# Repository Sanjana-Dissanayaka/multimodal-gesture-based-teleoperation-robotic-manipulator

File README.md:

# Multimodal Gesture-Based Teleoperation Framework for Low-Cost Robotic Manipulators

A low-cost gesture-based robotic teleoperation framework designed to provide an intuitive human–robot interaction interface using a wearable sensor glove.

The current system combines an **MPU6050 inertial measurement unit (IMU)** and **flex sensors** with calibration, filtering, gesture recognition, VPython hand visualization, and inverse-kinematics-based robotic manipulator control.

The framework is being extended toward a **hybrid multimodal teleoperation system** by integrating computer-vision-based hand tracking and physical robotic manipulator validation.

---

## Project Overview

Conventional robotic manipulator teleoperation interfaces such as joysticks and teach pendants can be less intuitive when operators need to perform natural hand-based manipulation.

Gesture-based interfaces provide a more natural method of communicating human intent to a robotic system. However, systems that depend on only one sensing method may experience problems such as:

* Sensor drift
* Measurement noise
* Camera occlusion
* Lighting variation
* Limited gesture information
* High implementation cost
* Reduced teleoperation accuracy

This project investigates a low-cost teleoperation framework that initially uses a wearable **IMU + flex-sensor glove** and is designed to later combine wearable sensing with computer vision.

---

## Overall Objective

Develop and validate a low-cost hybrid teleoperation system that integrates an **IMU + flex-sensor glove** with computer-vision-based hand tracking to achieve robust, accurate, and intelligent robotic manipulator control.

---

## System Architecture

The current teleoperation pipeline can be represented as:

```text
Human Hand
    │
    ▼
IMU + Flex Sensor Glove
    │
    ▼
Microcontroller / Data Acquisition
    │
    ▼
Calibration + Filtering
    │
    ▼
Gesture Recognition + Orientation Estimation
    │
    ├──────────────► VPython Virtual Hand
    │
    ▼
Gesture / Orientation Command Mapping
    │
    ▼
Inverse Kinematics
    │
    ▼
Robotic Manipulator Simulation
    │
    ▼
Sorting / Pick-and-Place Tasks
```

The planned multimodal extension is:

```text
Wearable Sensor Glove ──────┐
                            │
                            ▼
                    Hybrid Sensor Fusion
                            ▲
                            │
RGB Camera + MediaPipe ─────┘
                            │
                            ▼
                Robotic Manipulator Control
```

---

## Current Implementation

### 1. Wearable Sensing Layer

The wearable glove provides information about hand orientation and finger movement.

**MPU6050 IMU**

Used to estimate:

* Roll
* Pitch
* Yaw

**Flex Sensors**

Used to detect:

* Finger bending
* Open-hand gestures
* Closed-hand gestures
* Finger-count gestures
* Object-selection commands

---

## 2. Sensor Acquisition and Stabilization

Raw sensor data can contain noise, offsets, and small fluctuations.

The system therefore applies:

* Startup neutral calibration
* Flex-sensor calibration
* IMU calibration
* Deadband processing
* First-order smoothing
* Gesture stabilization
* Threshold-based gesture classification

These techniques improve the stability of commands before they are transmitted to the robotic manipulator.

---

## 3. Flex-Sensor Gesture Validation

The current gesture-validation criteria include:

| Condition           | Approximate Threshold |
| ------------------- | --------------------: |
| Straight finger     |                 ≤ 25° |
| Bent finger         |                 ≥ 60° |
| Stable gesture hold |                 0.5 s |

A gesture must remain sufficiently stable before it is accepted as a control command.

This helps prevent accidental commands caused by temporary sensor fluctuations.

---

## 4. Gesture Mapping

Finger gestures are mapped to object-selection and manipulation commands.

| Gesture   | Command              |
| --------- | -------------------- |
| 1 finger  | Select RED object    |
| 2 fingers | Select BLUE object   |
| 3 fingers | Select GREEN object  |
| 4 fingers | Select YELLOW object |
| Fist      | PICK                 |
| Open palm | PLACE / RELEASE      |

This allows the operator to select and manipulate objects using natural hand gestures.

---

## 5. IMU Orientation Mapping

The MPU6050 provides orientation information for controlling the manipulator end effector.

| Human-Hand Motion | Robot Command      |
| ----------------- | ------------------ |
| Roll              | End-effector roll  |
| Pitch             | End-effector pitch |
| Yaw               | End-effector yaw   |

Control limits are applied to prevent unrealistic or unstable manipulator commands.

### Current Safety Limits

| Motion       | Limit |
| ------------ | ----: |
| Roll         |  ±35° |
| Pitch        |  ±35° |
| Yaw          |  ±60° |
| Command rate | 25 Hz |

---

## 6. Virtual Hand Validation

Before controlling the robotic manipulator, sensor information is visualized using **VPython**.

The virtual-hand environment is used to validate:

* Finger bending
* Hand orientation
* Open-palm detection
* Fist detection
* Finger-count gestures
* Sensor calibration
* Gesture stability

This provides an intermediate validation stage between the physical glove and robotic manipulator.

---

## 7. Robotic Manipulator Simulation

Robotic manipulation is investigated using simulation environments such as:

* PyBullet
* CoppeliaSim

The simulation stage includes:

* Manipulator kinematics
* Forward kinematics
* Inverse kinematics
* End-effector orientation control
* Gesture-to-command mapping
* Object selection
* Pick-and-place operations
* Object sorting
* Contact-based manipulation experiments

---

## Inverse Kinematics

The desired end-effector pose generated from the gesture interface is converted into manipulator joint commands using inverse kinematics.

The general control process is:

```text
Human Gesture
      ↓
Target End-Effector Pose
      ↓
Inverse Kinematics
      ↓
Required Joint Angles
      ↓
Manipulator Motion
```

Inverse kinematics allows intuitive hand commands to be translated into feasible robotic manipulator movements.

---

## Hardware

The project hardware platform includes or investigates:

* MPU6050 IMU
* Flex sensors
* Wearable glove
* Microcontroller
* Custom PCB
* CH340G USB communication interface
* Flex-sensor interface circuitry
* Sensor wiring and connectors
* Robotic manipulator for final physical testing
* RGB camera for the planned vision stage

---

## Software and Development Tools

### Current Tools

* Python
* VPython
* PyBullet
* CoppeliaSim
* Arduino IDE
* KiCad
* Git
* GitHub

### Planned Vision Tools

* OpenCV
* MediaPipe

### Analysis and Evaluation

* Python
* MATLAB

---

## Major Development Phases

### Phase 1 – Wearable Hardware Development

* System architecture development
* PCB design
* Embedded firmware
* Hardware integration

### Phase 2 – Sensor Acquisition and Calibration

* MPU6050 calibration
* Flex-sensor calibration
* Noise filtering
* Gesture stabilization
* Wearable glove fabrication

### Phase 3 – Virtual Hand and Manipulator Validation

* VPython visualization
* Gesture mapping
* Teleoperation data acquisition
* Manipulator simulation
* Inverse-kinematics control

### Phase 4 – Vision-Based Teleoperation

Planned development includes:

* MediaPipe hand tracking
* Vision gesture recognition
* Vision-only manipulator control
* Performance comparison with the sensor glove

### Phase 5 – Hybrid Sensor Fusion

The future multimodal framework will combine:

```text
IMU
 +
Flex Sensors
 +
Computer Vision
        ↓
Hybrid Gesture Estimation
        ↓
Robotic Manipulator Control
```

The aim is to improve robustness against problems such as sensor drift and camera occlusion.

### Phase 6 – Physical Robot Integration

The final stage is intended to include:

* Physical robotic manipulator integration
* Wireless master–slave communication
* Servo-control optimization
* Real-time physical teleoperation
* Pick-and-place experiments
* Robustness testing
* Latency measurement
* Trajectory analysis
* Statistical evaluation

---

## Key Features

* Low-cost wearable gesture interface
* MPU6050-based hand orientation estimation
* Flex-sensor finger-motion measurement
* Sensor calibration
* Deadband processing
* Signal smoothing
* Stable gesture detection
* VPython virtual-hand visualization
* Gesture-labelled object selection
* Inverse-kinematics-based manipulator control
* PyBullet/CoppeliaSim simulation
* Pick-and-place control
* Object sorting
* Extendable multimodal architecture
* Planned MediaPipe computer-vision integration
* Designed for physical robotic-manipulator validation

---

## Research Contribution

The current framework provides a practical foundation for an intuitive and cost-effective human–robot teleoperation interface.

The main research direction is the development of a multimodal system that combines the advantages of wearable sensors and computer vision.

Potential benefits include:

* Improved teleoperation robustness
* Reduced dependence on conventional joysticks
* Natural human–robot interaction
* Improved resistance to camera occlusion
* Compensation for wearable-sensor drift
* Low implementation cost
* Flexible gesture-to-robot mapping

---

---
 ## Project Status

### Completed / Demonstrated

* Wearable gesture-glove prototype
* MPU6050 sensor acquisition
* Flex-sensor acquisition
* Sensor calibration
* Signal smoothing and deadband
* Gesture recognition
* VPython virtual-hand visualization
* Gesture-to-command mapping
* Manipulator simulation
* Inverse-kinematics-based control
* Gesture-controlled sorting and pick-and-place demonstrations

### Next Development Stage

* RGB-camera integration
* MediaPipe hand tracking
* Vision-only teleoperation
* Comparison between glove and vision systems
* Hybrid sensor fusion
* Physical robotic manipulator integration
* Experimental performance evaluation

---

## Future Improvements

* MediaPipe hand-landmark tracking
* Adaptive multimodal sensor fusion
* Vision and wearable-sensor synchronization
* Automatic sensor-drift compensation
* Kalman or complementary filtering
* Improved gesture-classification algorithms
* Wireless glove communication
* Physical 6-DoF manipulator integration
* End-effector camera feedback
* Collision avoidance
* Workspace constraints
* Trajectory smoothing
* Latency optimization
* Gesture confusion-matrix analysis
* Quantitative trajectory-error analysis
* User-based teleoperation experiments

---

## Contributors

### Lowe W.N.D.

**Registration No.: 2022/E/172**

Primary areas include:

* Embedded electronics
* PCB development
* IMU and flex-sensor calibration
* Python development
* Sensor fusion
* Teleoperation implementation
* Experimental evaluation

### Dissanayaka W.A.M.S.K.

**Registration No.: 2022/E/174**

Primary areas include:

* VPython visualization
* PyBullet simulation
* Computer vision
* MediaPipe implementation
* Mechanical fabrication
* Sensor-fusion development
* Experimental evaluation
* Documentation

---

## Supervisors

**Supervisor:** Mr. M. Barathraj
**Co-Supervisor:** Mr. P. Ravivarman

Department of Electrical & Electronic Engineering
Faculty of Engineering
University of Jaffna

---

## License

An open-source license has not yet been specified for this research project.

Because the repository contains collaborative university research work, an appropriate license should be selected only after agreement among the project contributors and relevant supervisors.

---

## Acknowledgements

This project is being developed as part of the undergraduate research work of the **Department of Electrical & Electronic Engineering, Faculty of Engineering, University of Jaffna**.

The authors acknowledge the guidance and support provided by the project supervisor and co-supervisor throughout the development of the gesture-based robotic teleoperation framework.

---

**Project:** Gesture-Based Teleoperation of a Robotic Manipulator
**Research Direction:** Low-Cost Hybrid Gesture-Based Teleoperation Using Wearable Sensor Fusion and Computer Vision

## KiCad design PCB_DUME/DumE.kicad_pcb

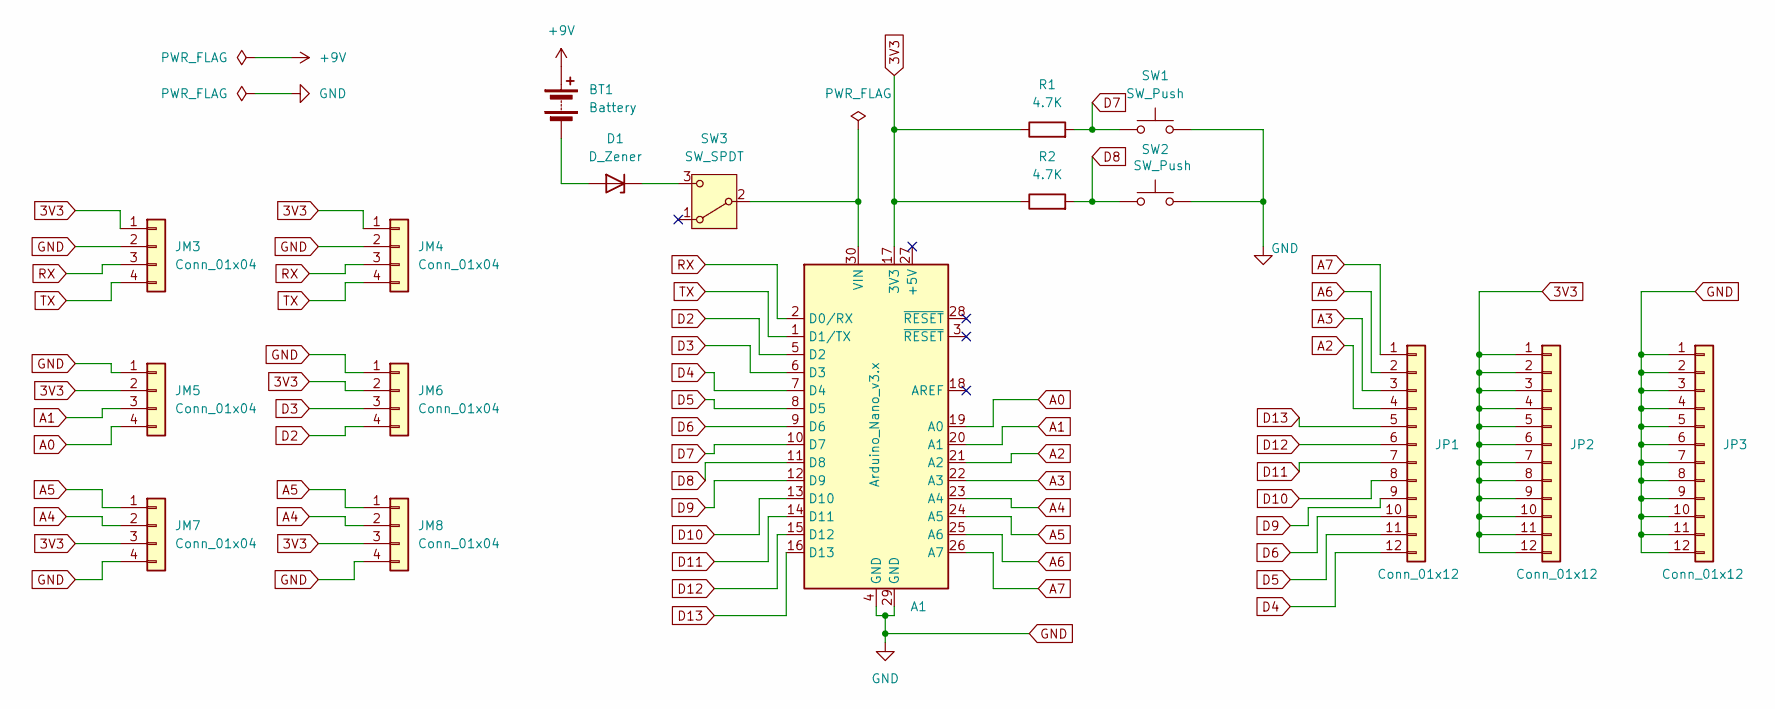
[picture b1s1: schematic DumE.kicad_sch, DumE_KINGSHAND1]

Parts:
A1: Arduino_Nano_v3.x; Arduino_Nano
BT1: Battery; BatteryHolder_Eagle_12BH611-GR
D1: D_Zener; D_0603_1608Metric
JM3, JM4, JM5, JM6, JM7, JM8: Conn_01x04; PinSocket_1x04_P2.54mm_Vertical
JP1, JP2, JP3: Conn_01x12; PinHeader_1x12_P2.54mm_Vertical
R1, R2: 4.7K; R_0603_1608Metric
SW1, SW2: SW_Push; SW_SPST_CK_RS282G05A3
SW3: SW_SPDT; SW_DIP_SPSTx01_Slide_Copal_CVS-01xB_W5.9mm_P1mm

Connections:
3V3: A1.17 (3V3), JM3.1, JM4.1, JM5.2, JM6.2, JM7.3, JM8.3, JP2.1, JP2.2, JP2.3, JP2.4, JP2.5, JP2.6, JP2.7, JP2.8, JP2.9, JP2.10, JP2.11, JP2.12, R1.1, R2.1
+9V: BT1.1 (+)
A0: A1.19 (A0), JM5.4
A1: A1.20 (A1), JM5.3
A2: A1.21 (A2), JP1.4
A3: A1.22 (A3), JP1.3
A4: A1.23 (A4), JM7.2, JM8.2
A5: A1.24 (A5), JM7.1, JM8.1
A6: A1.25 (A6), JP1.2
A7: A1.26 (A7), JP1.1
D2: A1.5 (D2), JM6.4
D3: A1.6 (D3), JM6.3
D4: A1.7 (D4), JP1.12
D5: A1.8 (D5), JP1.11
D6: A1.9 (D6), JP1.10
D7: A1.10 (D7), R1.2, SW1.1
D8: A1.11 (D8), R2.2, SW2.1
D9: A1.12 (D9), JP1.9
D10: A1.13 (D10), JP1.8
D11: A1.14 (D11), JP1.7
D12: A1.15 (D12), JP1.6
D13: A1.16 (D13), JP1.5
GND: A1.4 (GND), A1.29 (GND), JM3.2, JM4.2, JM5.1, JM6.1, JM7.4, JM8.4, JP3.1, JP3.2, JP3.3, JP3.4, JP3.5, JP3.6, JP3.7, JP3.8, JP3.9, JP3.10, JP3.11, JP3.12, SW1.2, SW2.2
unnamed: A1.30 (VIN), SW3.2 (B)
unnamed: BT1.2 (-), D1.2 (A)
unnamed: D1.1 (K), SW3.3 (C)
RX: A1.2 (D0/RX), JM3.3, JM4.3
TX: A1.1 (D1/TX), JM3.4, JM4.4

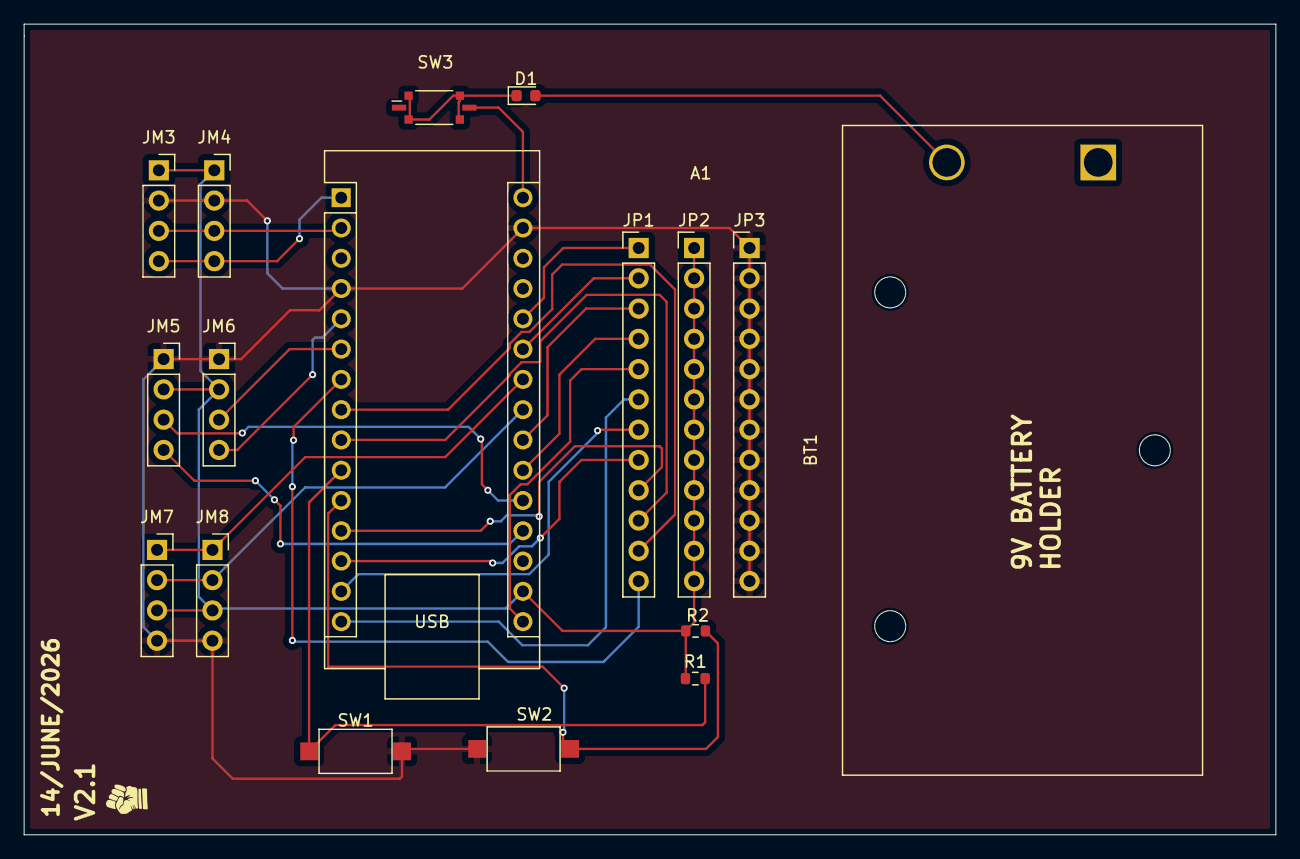
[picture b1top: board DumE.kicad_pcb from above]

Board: 2 copper layers, 105.0 x 68.0 mm, 17 parts (0 on the bottom side), 27 nets.
